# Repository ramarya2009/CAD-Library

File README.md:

CAD Library
===========

A selection of CAD drawings for off the shelf parts, several parametric
enclosure designs and a few things I have made which may be of use to others.

The selection of things is now [here](https://github.com/DanNixon/CAD-Things).

Notes
-----

Note that not all dimensions are guaranteed to be accurate, always double check
before manufacture.

Pin labels usually list special functions first and disregard generic functions
(e.g. RasPi pin 3 is labelled as SDA, not GPIO 0/2).

Credits
-------

- Raspberry Pi main board was adapted from DXF found
  [here](http://www.raspberry-projects.com/pi/pi-hardware/model-b-cad).
- Raspberry Pi camera module mount was adapted from [this
  thing](http://www.thingiverse.com/thing:214466).
- Arduino KiCAD parts by [nicholasclewis](http://www.thingiverse.com/thing:6430)

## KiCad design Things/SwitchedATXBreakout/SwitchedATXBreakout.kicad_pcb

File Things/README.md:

Things
======

A variety of things I have created, some are fairly generic and could be used easily, others are a bit more purpose built.

Credits
-------

	-	```LivingHingeBox_3mmMDF.dxf``` was originally designed by Paul Nixon.

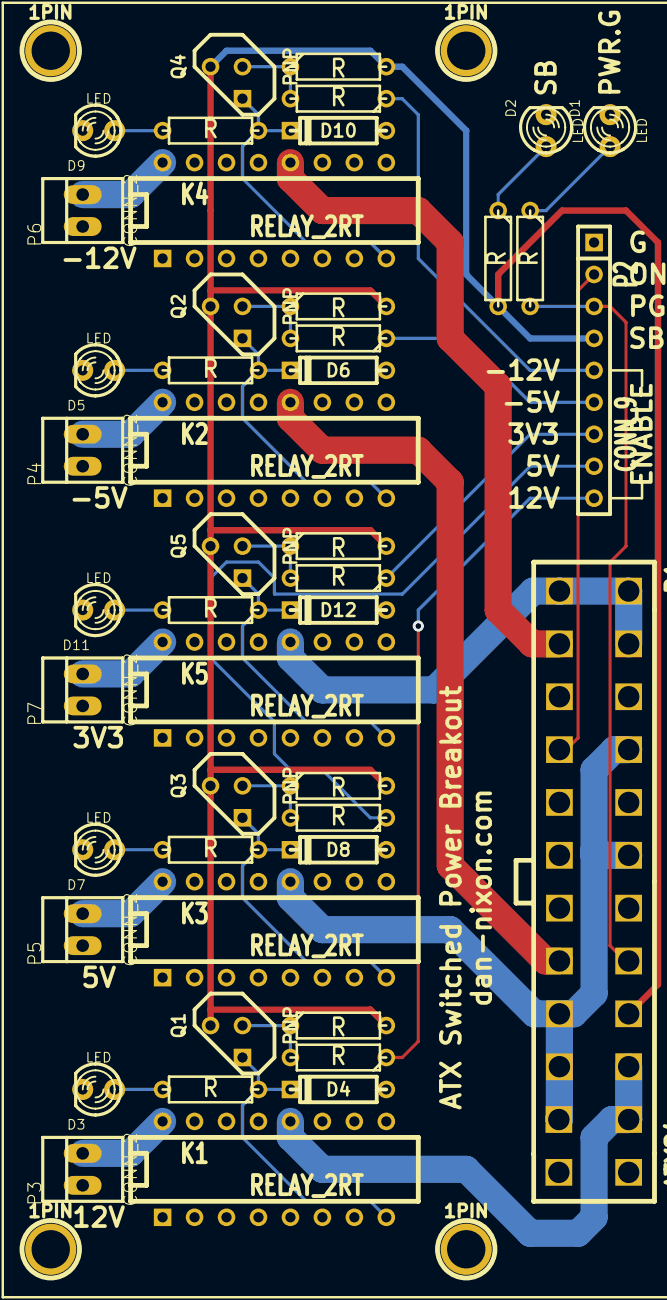
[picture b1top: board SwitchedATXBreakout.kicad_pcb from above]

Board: 2 copper layers, 50 parts (0 on the bottom side), 36 nets.

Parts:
1PIN, 1PIN#2, 1PIN#3, 1PIN#4: P***; 1pin
D1, D2, D3, D5, D7, D9, D11: LED; LED-3MM
D4, D6, D8, D10, D12: DIODE; D3
K1, K2, K3, K4, K5: RELAY_2RT; DIP-16__300
P1: ATX24
P2: CONN_9; SIL-9
P3, P4, P5, P6, P7: CONN_2; PINHEAD1-2
Q1, Q2, Q3, Q4, Q5: PNP; TO92
R1, R2, R3, R4, R5, R6, R7, R8, R9, R10, R11, R12, R13, R14, R15, R16, R17: R; R3

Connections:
3V3: K5.12, P1.1, P1.2, P1.3
+5V: K3.12, P1.7, P1.11, P1.18, P1.20, P1.22
+12V: K1.12, P1.19, P1.21
-5V: K2.12, P1.16
-12V: K4.12, P1.4
/3V3_EN: P2.7, R11.1
/3V3_OUT: K5.16, P7.2
/5V_EN: P2.8, R7.1
/5V_OUT: K3.16, P5.2
/5V_SB: P1.17, P2.4, Q1.3, Q2.3, Q3.3, Q4.3, Q5.3, R2.2, R13.2, R14.2, R15.2, R16.2, R17.2
/12V_EN: P2.9, R3.1
/12V_OUT: K1.16, P3.2
/-5V_EN: P2.6, R5.1
/-5V_OUT: K2.16, P4.2
/-12V_EN: P2.5, R9.1
/-12V_OUT: K4.16, P6.2
/PWR_GOOD: P1.15, P2.3, R1.2
/PWR_ON: P1.8, P2.2
GND: D1.2, D2.2, D3.2, D4.1, D5.2, D6.1, D7.2, D8.1, D9.2, D10.1, D11.2, D12.1, K1.9, K2.9, K3.9, K4.9, K5.9, P1.5, P1.6, P1.9, P1.10, P1.12, P1.13, P1.14, P2.1, P3.1, P4.1, P5.1, P6.1, P7.1
unnamed: D2.1, R2.1
unnamed: D1.1, R1.1
unnamed: D10.2, K4.8, Q4.1, R10.1
unnamed: D9.1, R10.2
unnamed: D6.2, K2.8, Q2.1, R6.1
unnamed: Q3.2, R7.2, R15.1
unnamed: Q2.2, R5.2, R14.1
unnamed: Q1.2, R3.2, R13.1
unnamed: Q4.2, R9.2, R16.1
unnamed: Q5.2, R11.2, R17.1
unnamed: D3.1, R4.2
unnamed: D8.2, K3.8, Q3.1, R8.1
unnamed: D7.1, R8.2
unnamed: D5.1, R6.2
unnamed: D12.2, K5.8, Q5.1, R12.1
unnamed: D11.1, R12.2
unnamed: D4.2, K1.8, Q1.1, R4.1

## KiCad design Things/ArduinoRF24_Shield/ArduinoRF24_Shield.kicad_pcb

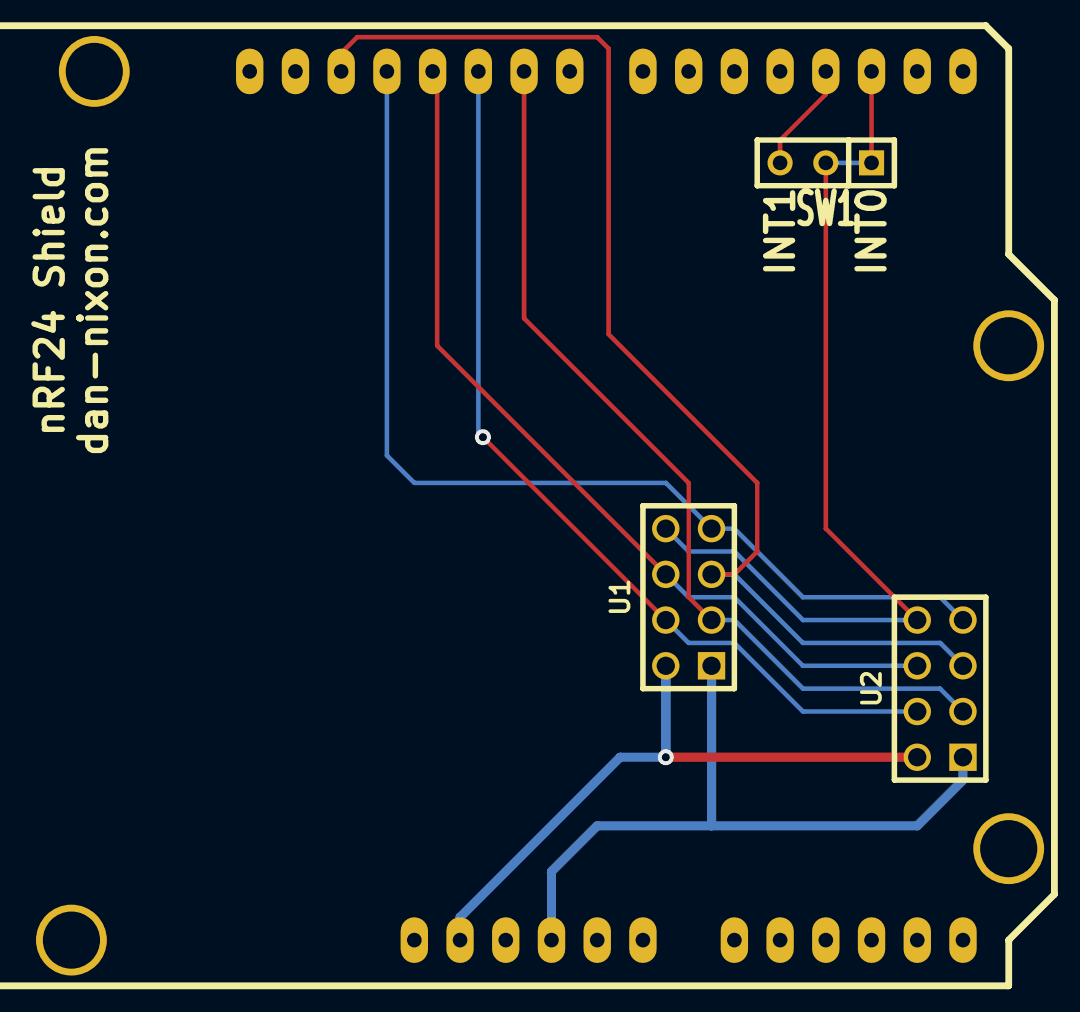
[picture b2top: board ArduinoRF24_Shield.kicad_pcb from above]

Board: 2 copper layers, 4 parts (0 on the bottom side), 9 nets.

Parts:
SHIELD1: ARDUINO_SHIELD; ARDUINO SHIELD
SW1: SWITCH_INV; SIL-3
U1, U2: NRF24; pin_array_4x2

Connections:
/3v3: SHIELD1.3V3, U1.2, U2.2
/CE: SHIELD1.9, U1.3, U2.3
/CSN: SHIELD1.10, U1.4, U2.4
/GND: SHIELD1.GND1, U1.1, U2.1
/IRQ: SHIELD1.2, SW1.1, SW1.2, U1.8, U2.8
/MISO: SHIELD1.12, U1.7, U2.7
/MOSI: SHIELD1.11, U1.6, U2.6
/SCK: SHIELD1.13, U1.5, U2.5
unnamed: SHIELD1.3, SW1.3

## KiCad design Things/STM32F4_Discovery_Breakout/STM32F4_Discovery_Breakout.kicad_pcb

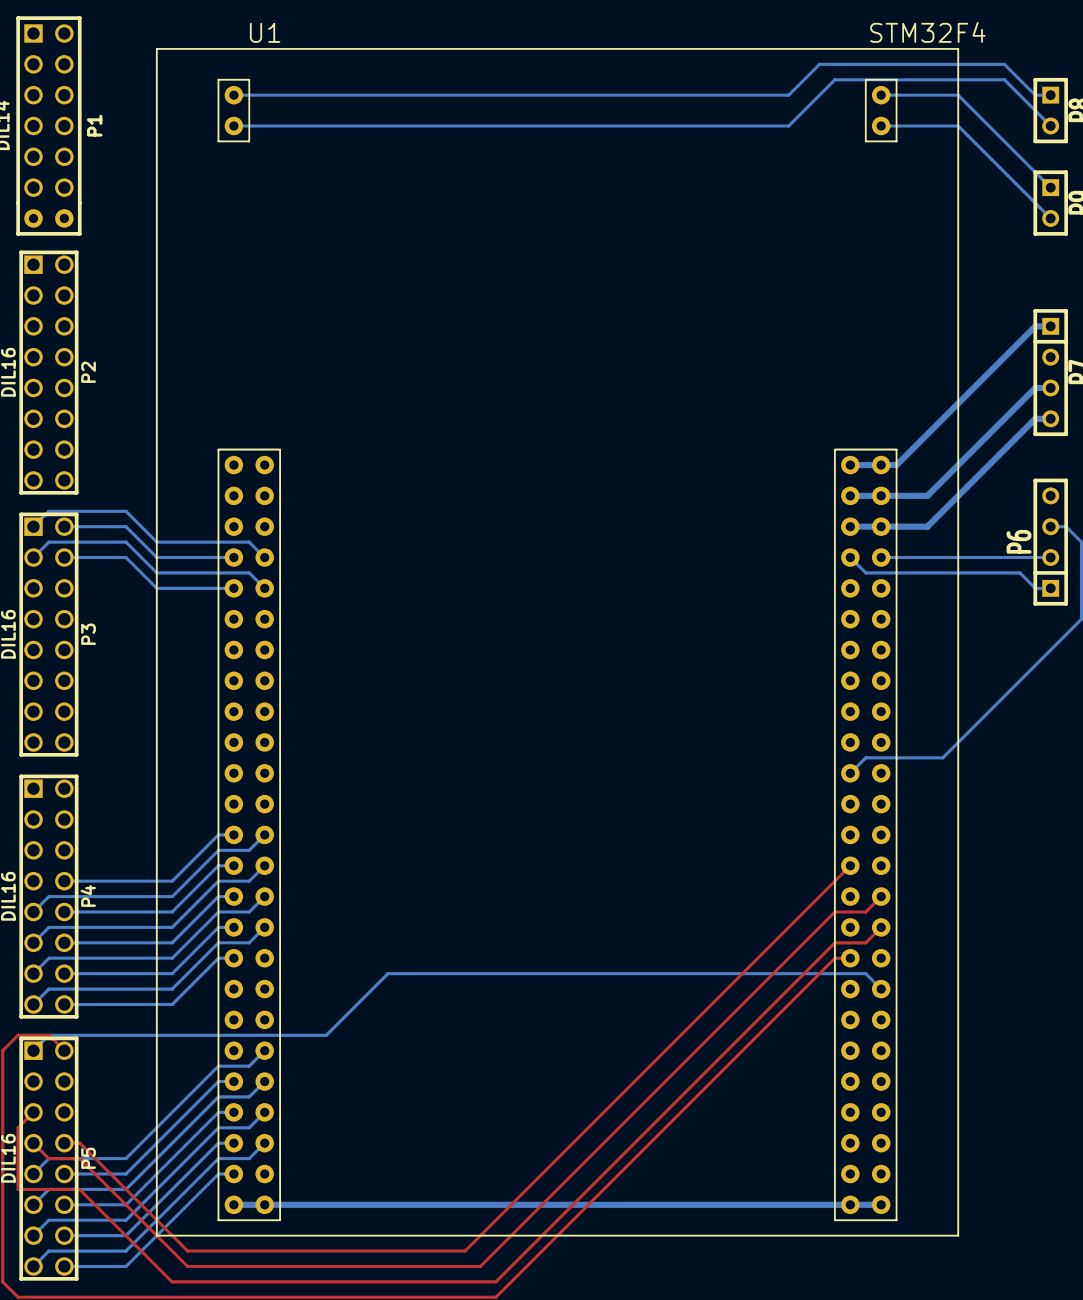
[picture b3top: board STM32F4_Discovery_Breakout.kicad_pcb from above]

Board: 2 copper layers, 10 parts (0 on the bottom side), 90 nets.

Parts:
P1: DIL14; pin_array_7x2
P2, P3, P4, P5: DIL16; pin_array_8x2
P6, P7: CONN_4; SIL-4
P8, P9: CONN_2; SIL-2
U1: STM32F4; STM32F4_mount

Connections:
unnamed: P2.11, U1.34
unnamed: P5.4, U1.66
unnamed: P5.3, U1.84
unnamed: P5.2, U1.67
unnamed: P5.16, U1.24
unnamed: P5.1, U1.83
unnamed: P2.12, U1.18
unnamed: P5.15, U1.28
unnamed: P2.10, U1.91
unnamed: P2.9, U1.60
unnamed: P2.13, U1.33
unnamed: P2.14, U1.19
unnamed: P5.6, U1.65
unnamed: P5.5, U1.85
unnamed: P5.8, U1.64
unnamed: P5.9, U1.31
unnamed: P5.10, U1.21
unnamed: P2.15, U1.32
unnamed: P5.11, U1.30
unnamed: P5.12, U1.22
unnamed: P5.13, U1.29
unnamed: P5.14, U1.23
unnamed: P3.3, U1.46
unnamed: P3.7, U1.74
unnamed: P3.6, U1.10
unnamed: P3.5, U1.41
unnamed: P3.4, U1.5
unnamed: P3.2, U1.4
unnamed: P3.1, U1.47
unnamed: P3.9, U1.73
unnamed: P3.10, U1.78
unnamed: P3.11, U1.69
unnamed: P2.16, U1.20
unnamed: P2.8, U1.89
unnamed: P2.7, U1.62
unnamed: P2.6, U1.88
unnamed: P2.5, U1.63
unnamed: P2.4, U1.87
unnamed: P2.3, U1.39
unnamed: P2.2, U1.11
unnamed: P2.1, U1.40
unnamed: P3.8, U1.77
unnamed: P1.5, U1.43
unnamed: P1.9, U1.72
unnamed: P1.8, U1.9
unnamed: P1.7, U1.42
unnamed: P1.6, U1.8
unnamed: P1.4, U1.7
unnamed: P1.3, U1.44
unnamed: P1.2, U1.6
unnamed: P1.12, U1.80
unnamed: P1.13, U1.70
unnamed: P6.1, U1.54
unnamed: P6.2, U1.97
unnamed: P6.3, U1.61
unnamed: P6.4, U1.48
unnamed: P1.11, U1.71
unnamed: P1.10, U1.79
unnamed: P4.4, U1.93
unnamed: P4.11, U1.37
unnamed: P4.12, U1.15
unnamed: P4.13, U1.36
unnamed: P4.14, U1.16
unnamed: P4.15, U1.35
unnamed: P4.16, U1.17
unnamed: P4.3, U1.58
unnamed: P4.2, U1.92
unnamed: P4.1, U1.59
unnamed: P5.7, U1.86
unnamed: P1.14, U1.81
unnamed: P1.1, U1.45
unnamed: P4.8, U1.13
unnamed: P4.7, U1.56
unnamed: P4.6, U1.94
unnamed: P4.5, U1.57
unnamed: P4.9, U1.38
unnamed: P4.10, U1.14
unnamed: P7.4, U1.53, U1.98
unnamed: P3.13, U1.68
unnamed: P3.16, U1.96
unnamed: P7.1, U1.1, U1.3, U1.12, U1.25, U1.26, U1.50, U1.51, U1.75, U1.76, U1.100
unnamed: P3.14, U1.95
unnamed: P9.2, U1.104
unnamed: P9.1, U1.103
unnamed: P8.2, U1.102
unnamed: P7.2, U1.2, U1.49, U1.90
unnamed: P3.15, U1.55
unnamed: P3.12, U1.82
unnamed: P7.3, U1.52, U1.99
unnamed: P8.1, U1.101

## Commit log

2014-01-09 Added repo info
2014-01-09 Added basic drawings for some dev boards
2014-01-10 Added gitignore and updated Arduino Mega
2014-01-10 Vastly improved dev board designs
2014-01-10 Started Arduino UNO
2014-01-10 Finished Arduino Uno DXF
2014-01-11 Renamed LIbreCAD to DXF
2014-01-11 Added Sparkfun MLP3115A2 altitude sensor breakout board
2014-01-11 Fixed folders
2014-01-11 Added new modules, updated structure
2014-01-11 Added more modules
2014-01-11 Rnamed iMall NRF module
2014-01-11 CHanged layer anmes of iMall nRF module
2014-01-17 Added Maplin microswitch
2014-01-19 Added pinout labelling to dev boards
2014-01-25 Added spacers
2014-02-08 Added Things
2014-02-22 Added BubbleScope bayonet mount
2014-02-23 Updated BubbleScope mount
2014-02-23 Added SMA connector mount
2014-02-26 Fix some 3D models
2014-03-05 Modified thicness of anteanna connector
2014-03-07 Added Parallax joystick DXF
2014-03-10 Updated Raspberry Pi server
2014-03-11 Added new spacers Finished tablet stand Updated Pi NAS box
2014-03-11 Finished rPi server NAS box
2014-03-11 Added custom KiCAD libs
2014-03-12 Added tablet retention clips for tablet stand
2014-03-12 Added SCAD primatives Added rounding to tablet stand clips
2014-03-12 Added more SCAD parts, updated BubbleScope mount
2014-03-13 Updated rounded rect, added PiCam mount, added end gcode to move head up after print
2014-03-13 Updated Bubblescope PiCam mount
2014-03-14 Added PiCam mount rear cover
2014-03-14 Updated BubbleScope PiCam mount, camera is closer to scope
2014-03-16 Updated BubbleScope mount threads
2014-03-17 Added ITEAD GLCD drawing
2014-03-22 Added ITEAD Arduino Mega clone board
2014-03-22 Updated GLCD drawingS
2014-03-23 Added some parts
2014-03-25 Added new components
2014-04-03 Added fan mounting to 4 motor design
2014-04-03 Updated flying duck text
2014-04-05 Added STM32F4 discovery board KiCAD files
2014-04-06 Modify WGAFD fan mounting angle
2014-04-07 Updated STM32 KiCAD part
2014-04-07 Fixed polar duck mount
2014-04-08 Added STM32 breakout board
2014-04-08 Updated STM32 breakout board
2014-04-13 Added proper name to WGAFD
2014-04-17 Small fix for WGAFD
2014-04-17 Updated flying duck drawings
2014-04-17 Added RasPi BubbleScope kit
2014-04-19 Part finished ODROID CAD file
2014-04-24 Updated PiCam BubbleScope mount
2014-04-24 Fixed BubbleScope mount issues
2014-04-25 Added joystick mounting panel
2014-04-26 Added laser focus tool
2014-04-29 Added Living Hinge things
2014-05-02 Added Bar Eastern binder
2014-05-05 Updated Bar Eastern binder
2014-05-06 Misc laser cutter stuff
2014-05-06 Added BarEastern binder LaserCut5.3 files
2014-05-07 Added BarEastern page cutout file
2014-05-07 Added treasury tag
2014-05-13 Added Arduino nRF24 shield
2014-05-14 Updated ATX breakout board
2014-05-15 Updated CAD drawings
2014-05-16 Updated CAD
2014-05-16 Moved the beam on sign
2014-05-21 Added pub alarm, updated ATX breakout board
2014-05-22 Updated Pi box and ATX board
2014-05-25 More ATX board layout
2014-05-25 More ATX PCB routing
2014-05-26 More PCB routing
2014-05-26 Wider traces for high power nets
2014-05-27 Added Flan HDD enclosure
2014-05-28 ATX board routing, added Trust webcam mount
2014-06-01 Adding pullups to ATX board
2014-06-04 Added ITEAD char LCD DXF
2014-06-13 Added more DXFs
2014-06-13 Added new DXF parts
    Micro servo and ITEAD 8x2 char. LCD
2014-06-16 Added more board DXFs
2014-06-16 Added more DXF parts
2014-06-22 Added Arduino MEGA VESA bracket
2014-06-23 Matrix jig
2014-06-26 Added parametric enclosures and living hinge
2014-06-27 Added Makefile for angled desk enclosure, refactoring
2014-06-29 Added more general use parametric living hinge
2014-06-29 Updated generic hinge
2014-06-30 Added ability to use multiple gap types in one LH design
2014-07-03 Buxfixes in generic living hinge
    Started generic n sided braced box
2014-07-04 Updated parametric enclosures
2014-07-04 More sensible dimensions for example
2014-08-03 Added 6 sided finger joint enclosure
2014-08-04 Updated docs
2014-08-04 Fix typo in readme
2014-08-04 Updated makefiles
2014-08-07 Initial copy of braced box
2014-08-07 Update docs
2014-08-07 Added finger joints to main panel
2014-08-10 Added MultiWii board
2014-08-30 Corrected angled desk panel
2014-11-08 Add another display module
2014-11-08 Correct layer colour
2014-12-17 Add generic M3 screw joint
2014-12-17 Added more parts
2015-03-12 Add downlaod scripts for public KiCAD libs
2015-03-12 Added OSHEC library download script
2015-03-12 Added ATX PS/2 mount
    Based on dimensions here:
    http://www.dynapowerusa.com/dyna/ProductWiki/1.asp
2015-03-12 Keep downloaded KiCAD libs separate
2015-03-12 Added some new switches
2015-03-16 Added panasonic relat EAGLE part
2015-03-24 Added additional Molex connectors
2015-03-26 New Molex part
2015-04-04 Update relay footprint
2015-04-04 Remove old ATX power PCB
2015-04-11 Added Alesis mixer drawing
2015-04-11 Add some more fixings
2015-04-11 Start work on an amplifier case
2015-04-11 More work on amplifier case
2015-04-13 Update amplifier case
2015-04-17 Added new cutout
2015-04-18 New parts
2015-04-18 Update text
2015-04-20 Correct size
2015-04-20 Update amp case
2015-04-20 Amp case CAD fixes
2015-04-21 Remove things, uodate README
2015-06-04 Added KobbyKIng KK Mini part
